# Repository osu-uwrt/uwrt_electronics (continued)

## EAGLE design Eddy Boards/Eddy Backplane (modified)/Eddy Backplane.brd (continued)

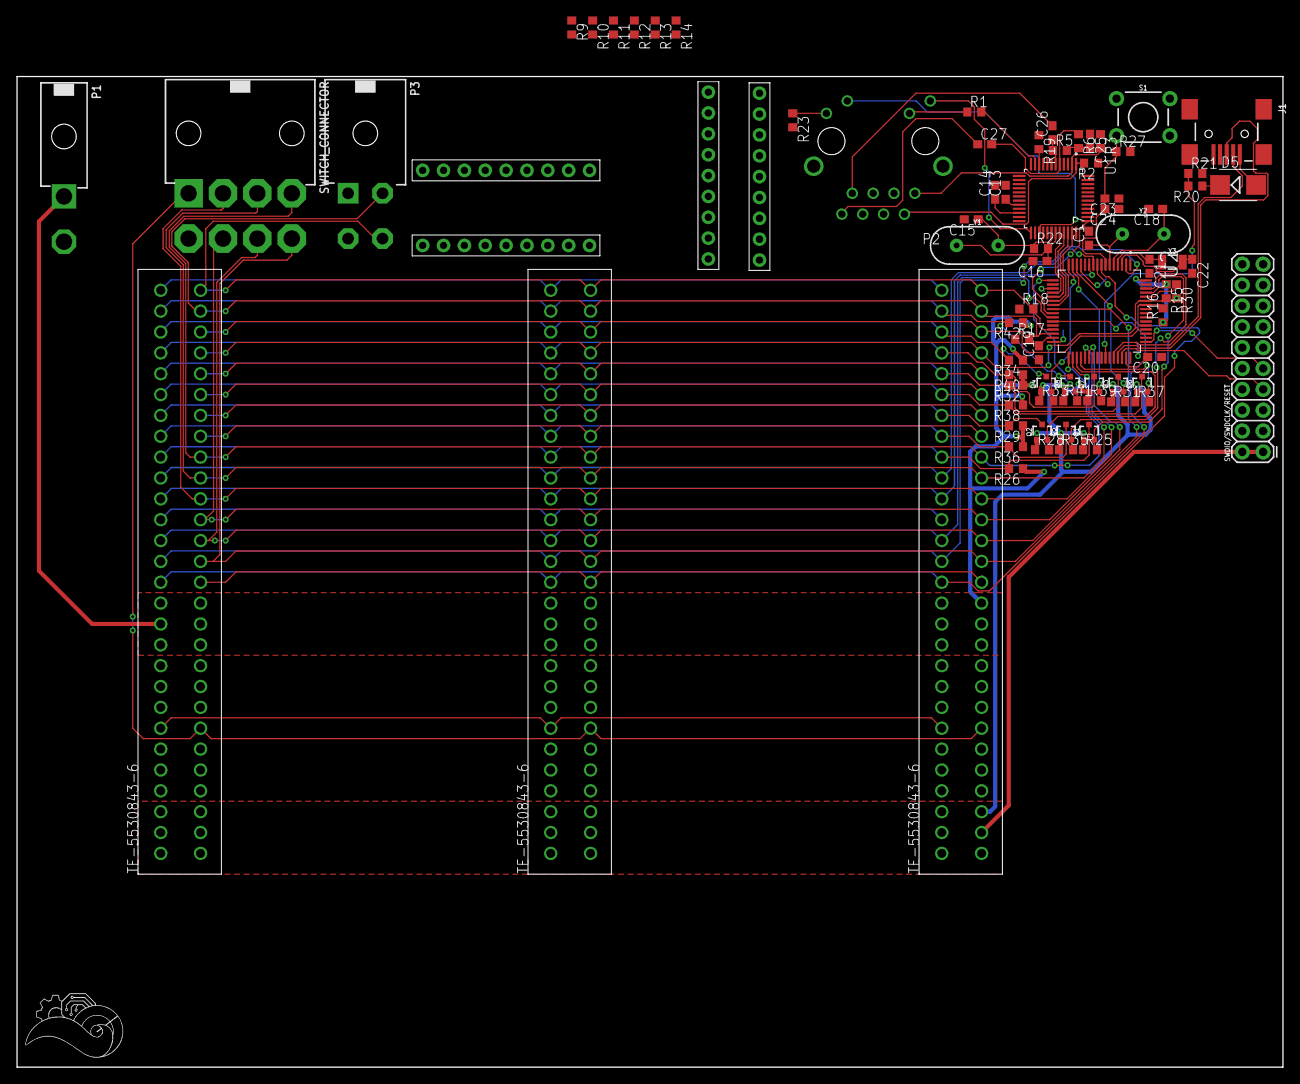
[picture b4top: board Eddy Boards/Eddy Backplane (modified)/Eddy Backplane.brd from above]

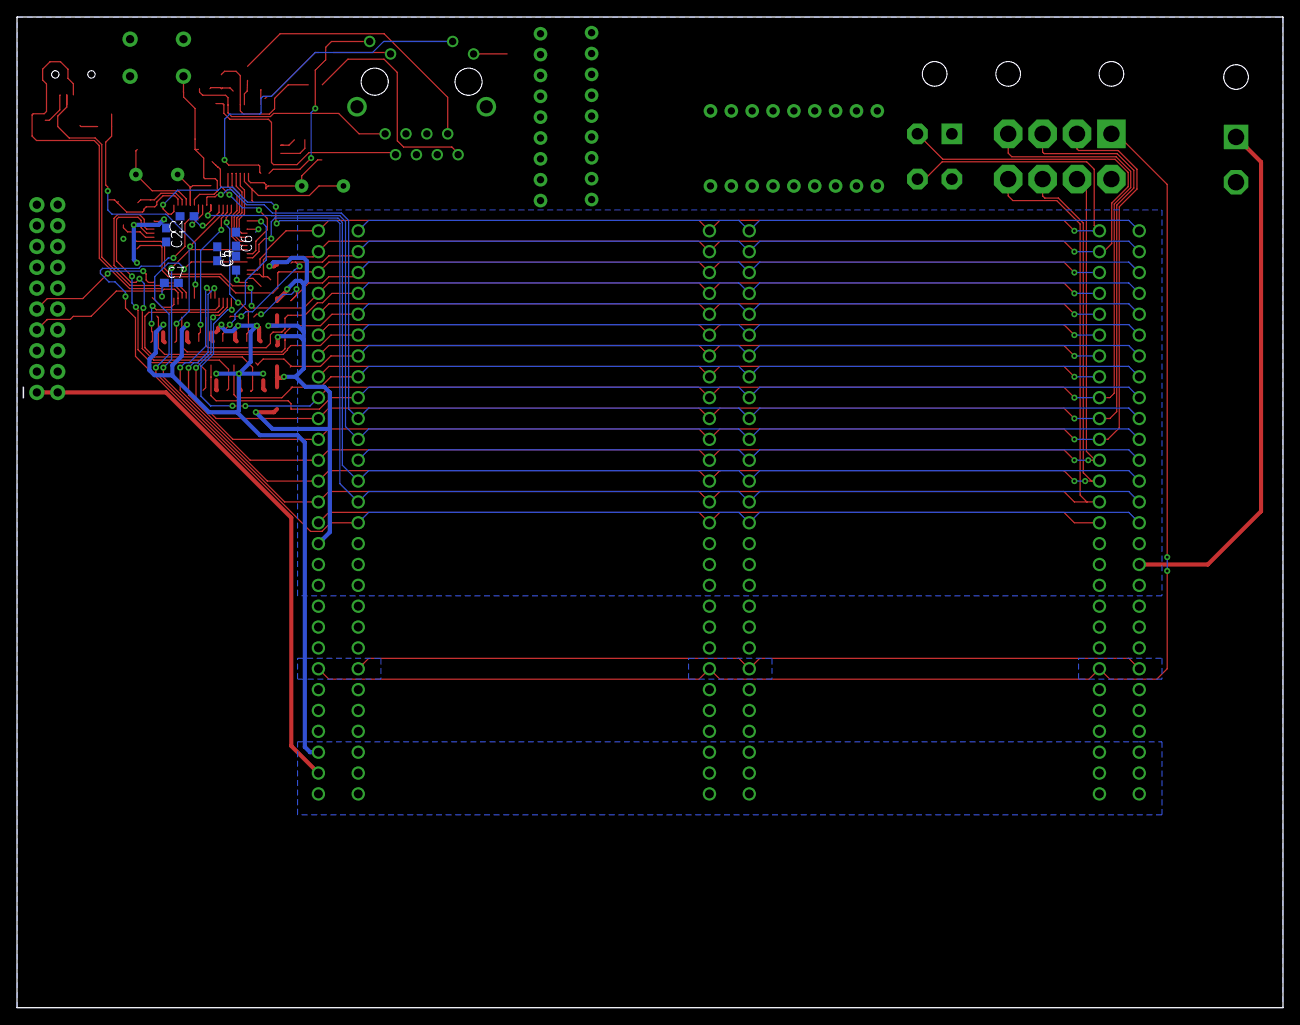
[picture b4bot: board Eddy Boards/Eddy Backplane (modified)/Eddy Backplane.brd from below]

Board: 2 copper layers, 154.2 x 120.7 mm, 87 parts (6 on the bottom side), 79 nets.

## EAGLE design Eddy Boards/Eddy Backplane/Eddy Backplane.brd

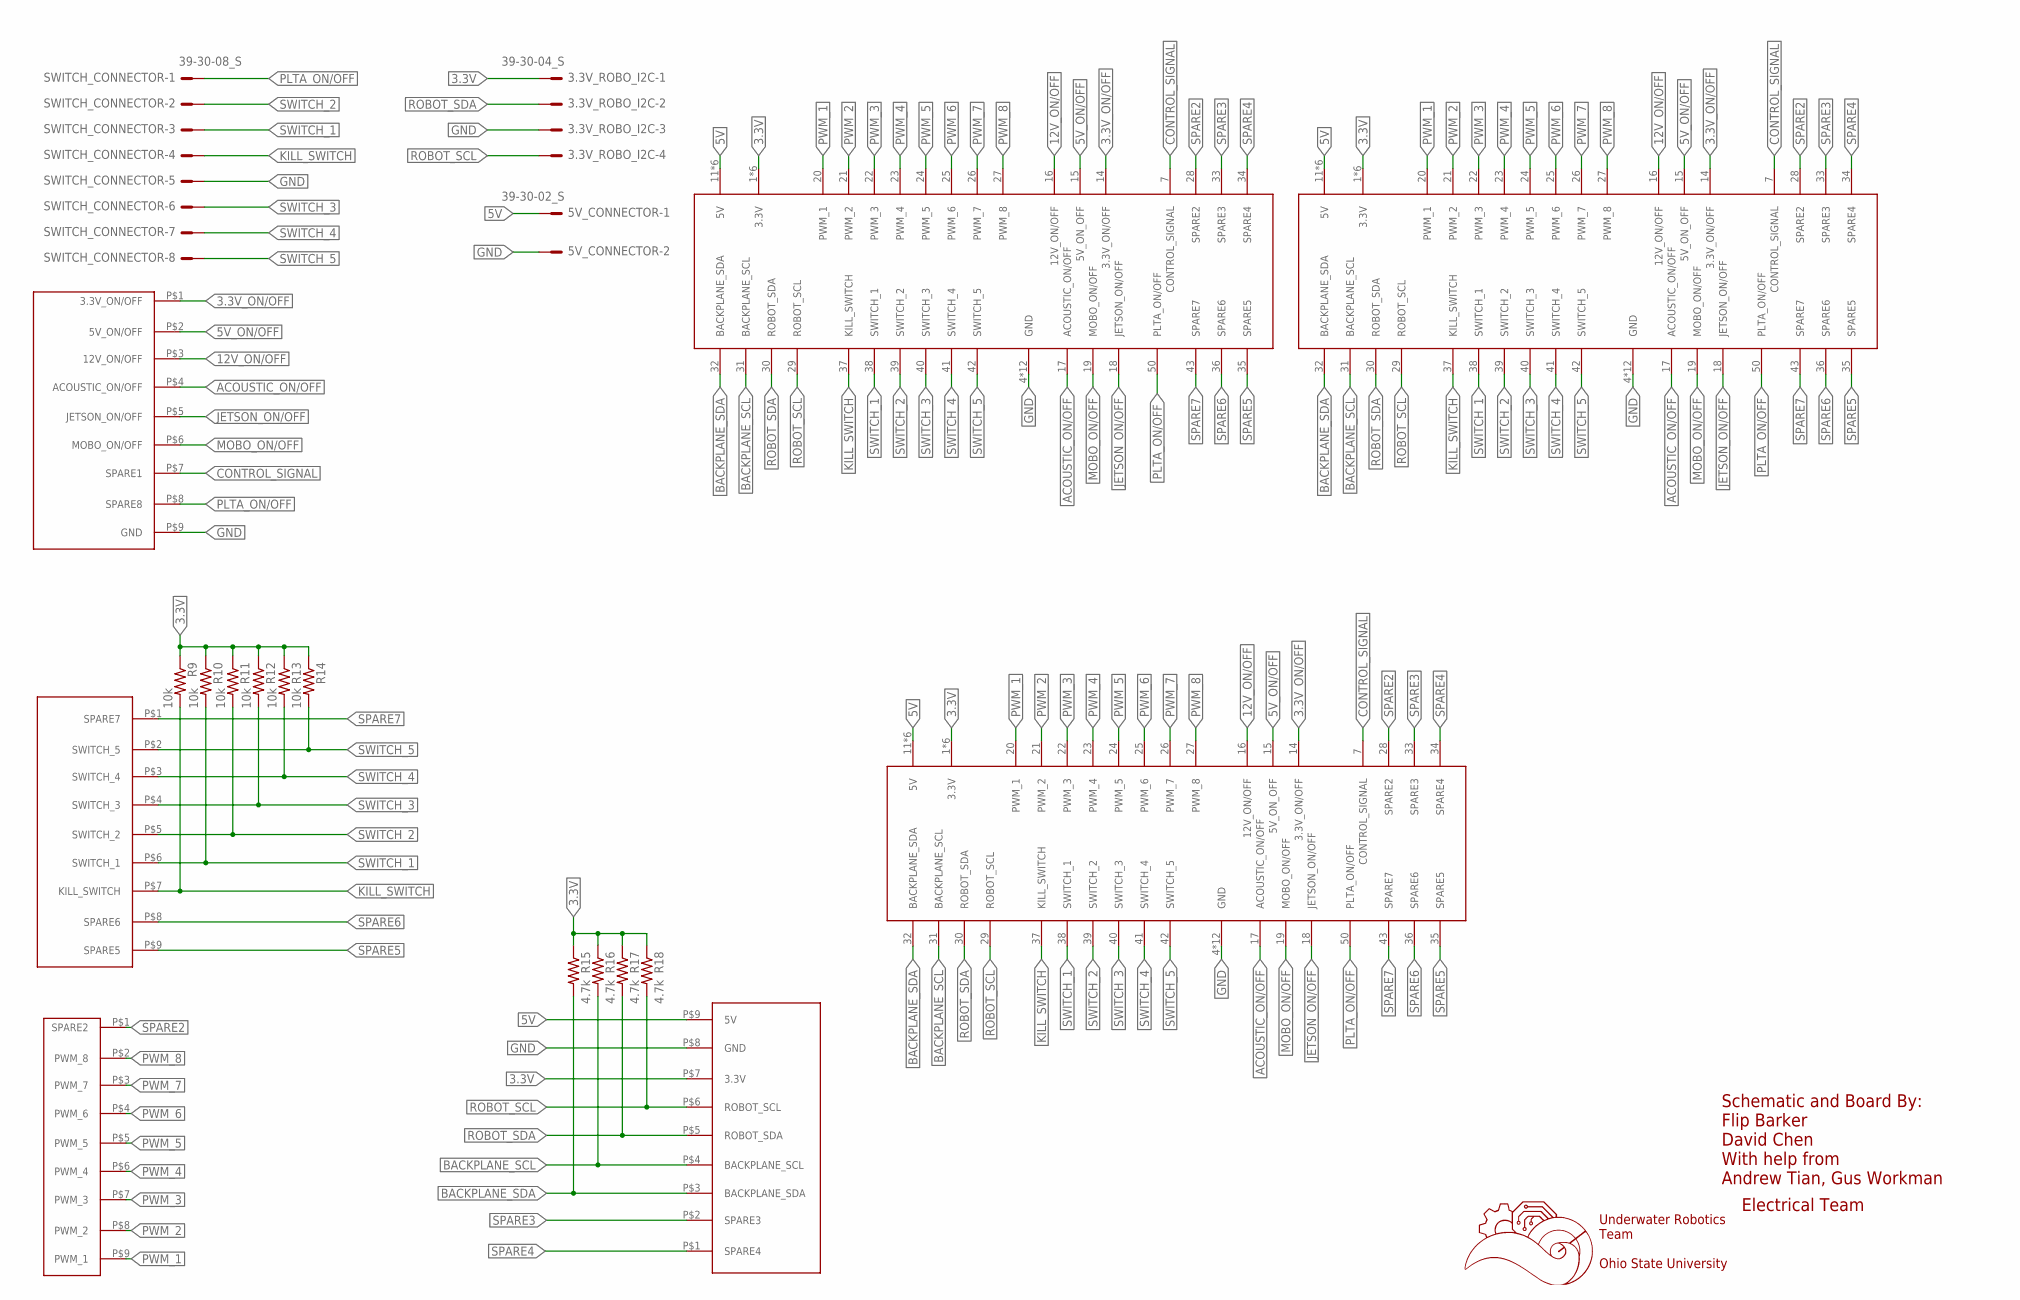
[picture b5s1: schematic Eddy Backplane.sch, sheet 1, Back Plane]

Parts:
3.3V_ROBO_I2C: 39-30-04_S; 39-30-?04?
5V_CONNECTOR: 39-30-02_S; 39-30-?02?
PWR_ON: 929870-01-09_3; 929852-01-09_1ROW
R9, R10, R11, R12, R13, R14: 10k; R0603
R15, R16, R17, R18: 4.7k; R0603
SWITCH_CONN: 929870-01-09_1; 929852-01-09_1ROW
SWITCH_CONNECTOR: 39-30-08_S; 39-30-?08?
U$1, U$2, U$3: 5530843-FEMALE; 5530843-6-BACKPLANEMATE
U$6: 929870-01-09_2; 929852-01-09_1ROW
U$8: 929870-01-09_4; 929852-01-09_1ROW

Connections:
3.3V: 3.3V_ROBO_I2C.1, R9.1, R10.1, R11.1, R12.1, R13.1, R14.1, R15.1, R16.1, R17.1, R18.1, U$1.1 (3.3V), U$1.2 (3.3V), U$1.3 (3.3V), U$1.54 (3.3V), U$1.55 (3.3V), U$1.56 (3.3V), U$2.1 (3.3V), U$2.2 (3.3V), U$2.3 (3.3V), U$2.54 (3.3V), U$2.55 (3.3V), U$2.56 (3.3V), U$3.1 (3.3V), U$3.2 (3.3V), U$3.3 (3.3V), U$3.54 (3.3V), U$3.55 (3.3V), U$3.56 (3.3V), U$8.P$7 (3.3V); also elsewhere on the board
3.3V_ON/OFF: PWR_ON.P$1 (3.3V_ON/OFF), U$1.14 (3.3V_ON/OFF), U$2.14 (3.3V_ON/OFF), U$3.14 (3.3V_ON/OFF); also elsewhere on the board
5V: 5V_CONNECTOR.1, U$1.11 (5V), U$1.12 (5V), U$1.13 (5V), U$1.44 (5V), U$1.45 (5V), U$1.46 (5V), U$2.11 (5V), U$2.12 (5V), U$2.13 (5V), U$2.44 (5V), U$2.45 (5V), U$2.46 (5V), U$3.11 (5V), U$3.12 (5V), U$3.13 (5V), U$3.44 (5V), U$3.45 (5V), U$3.46 (5V), U$8.P$9 (5V); also elsewhere on the board
5V_ON/OFF: PWR_ON.P$2 (5V_ON/OFF), U$1.15 (5V_ON_OFF), U$2.15 (5V_ON_OFF), U$3.15 (5V_ON_OFF); also elsewhere on the board
12V_ON/OFF: PWR_ON.P$3 (12V_ON/OFF), U$1.16 (12V_ON/OFF), U$2.16 (12V_ON/OFF), U$3.16 (12V_ON/OFF); also elsewhere on the board
ACOUSTIC_ON/OFF: PWR_ON.P$4 (ACOUSTIC_ON/OFF), U$1.17 (ACOUSTIC_ON/OFF), U$2.17 (ACOUSTIC_ON/OFF), U$3.17 (ACOUSTIC_ON/OFF)
BACKPLANE_SCL: R16.2, U$1.31 (BACKPLANE_SCL), U$2.31 (BACKPLANE_SCL), U$3.31 (BACKPLANE_SCL), U$8.P$4 (BACKPLANE_SCL); also elsewhere on the board
BACKPLANE_SDA: R15.2, U$1.32 (BACKPLANE_SDA), U$2.32 (BACKPLANE_SDA), U$3.32 (BACKPLANE_SDA), U$8.P$3 (BACKPLANE_SDA); also elsewhere on the board
CONTROL_SIGNAL: PWR_ON.P$7 (SPARE1), U$1.7 (CONTROL_SIGNAL), U$2.7 (CONTROL_SIGNAL), U$3.7 (CONTROL_SIGNAL); also elsewhere on the board
GND: 3.3V_ROBO_I2C.3, 5V_CONNECTOR.2, PWR_ON.P$9 (GND), SWITCH_CONNECTOR.5, U$1.4 (GND), U$1.5 (GND), U$1.6 (GND), U$1.8 (GND), U$1.9 (GND), U$1.10 (GND), U$1.47 (GND), U$1.48 (GND), U$1.49 (GND), U$1.51 (GND), U$1.52 (GND), U$1.53 (GND), U$2.4 (GND), U$2.5 (GND), U$2.6 (GND), U$2.8 (GND), U$2.9 (GND), U$2.10 (GND), U$2.47 (GND), U$2.48 (GND), U$2.49 (GND), U$2.51 (GND), U$2.52 (GND), U$2.53 (GND), U$3.4 (GND), U$3.5 (GND), U$3.6 (GND), U$3.8 (GND), U$3.9 (GND), U$3.10 (GND), U$3.47 (GND), U$3.48 (GND), U$3.49 (GND), U$3.51 (GND), U$3.52 (GND), U$3.53 (GND), U$8.P$8 (GND); also elsewhere on the board
JETSON_ON/OFF: PWR_ON.P$5 (JETSON_ON/OFF), U$1.18 (JETSON_ON/OFF), U$2.18 (JETSON_ON/OFF), U$3.18 (JETSON_ON/OFF); also elsewhere on the board
KILL_SWITCH: R9.2, SWITCH_CONN.P$7 (KILL_SWITCH), SWITCH_CONNECTOR.4, U$1.37 (KILL_SWITCH), U$2.37 (KILL_SWITCH), U$3.37 (KILL_SWITCH); also elsewhere on the board
MOBO_ON/OFF: PWR_ON.P$6 (MOBO_ON/OFF), U$1.19 (MOBO_ON/OFF), U$2.19 (MOBO_ON/OFF), U$3.19 (MOBO_ON/OFF); also elsewhere on the board
PLTA_ON/OFF: PWR_ON.P$8 (SPARE8), SWITCH_CONNECTOR.1, U$1.50 (PLTA_ON/OFF), U$2.50 (PLTA_ON/OFF), U$3.50 (PLTA_ON/OFF)
PWM_1: U$1.20 (PWM_1), U$2.20 (PWM_1), U$3.20 (PWM_1), U$6.P$9 (PWM_1); also elsewhere on the board
PWM_2: U$1.21 (PWM_2), U$2.21 (PWM_2), U$3.21 (PWM_2), U$6.P$8 (PWM_2); also elsewhere on the board
PWM_3: U$1.22 (PWM_3), U$2.22 (PWM_3), U$3.22 (PWM_3), U$6.P$7 (PWM_3); also elsewhere on the board
PWM_4: U$1.23 (PWM_4), U$2.23 (PWM_4), U$3.23 (PWM_4), U$6.P$6 (PWM_4); also elsewhere on the board
PWM_5: U$1.24 (PWM_5), U$2.24 (PWM_5), U$3.24 (PWM_5), U$6.P$5 (PWM_5); also elsewhere on the board
PWM_6: U$1.25 (PWM_6), U$2.25 (PWM_6), U$3.25 (PWM_6), U$6.P$4 (PWM_6); also elsewhere on the board
PWM_7: U$1.26 (PWM_7), U$2.26 (PWM_7), U$3.26 (PWM_7), U$6.P$3 (PWM_7); also elsewhere on the board
PWM_8: U$1.27 (PWM_8), U$2.27 (PWM_8), U$3.27 (PWM_8), U$6.P$2 (PWM_8); also elsewhere on the board
ROBOT_SCL: 3.3V_ROBO_I2C.4, R18.2, U$1.29 (ROBOT_SCL), U$2.29 (ROBOT_SCL), U$3.29 (ROBOT_SCL), U$8.P$6 (ROBOT_SCL); also elsewhere on the board
ROBOT_SDA: 3.3V_ROBO_I2C.2, R17.2, U$1.30 (ROBOT_SDA), U$2.30 (ROBOT_SDA), U$3.30 (ROBOT_SDA), U$8.P$5 (ROBOT_SDA); also elsewhere on the board
SPARE2: U$1.28 (SPARE2), U$2.28 (SPARE2), U$3.28 (SPARE2), U$6.P$1 (SPARE2)
SPARE3: U$1.33 (SPARE3), U$2.33 (SPARE3), U$3.33 (SPARE3), U$8.P$2 (SPARE3)
SPARE4: U$1.34 (SPARE4), U$2.34 (SPARE4), U$3.34 (SPARE4), U$8.P$1 (SPARE4)
SPARE5: SWITCH_CONN.P$9 (SPARE5), U$1.35 (SPARE5), U$2.35 (SPARE5), U$3.35 (SPARE5)
SPARE6: SWITCH_CONN.P$8 (SPARE6), U$1.36 (SPARE6), U$2.36 (SPARE6), U$3.36 (SPARE6)
SPARE7: SWITCH_CONN.P$1 (SPARE7), U$1.43 (SPARE7), U$2.43 (SPARE7), U$3.43 (SPARE7)
SWITCH_1: R10.2, SWITCH_CONN.P$6 (SWITCH_1), SWITCH_CONNECTOR.3, U$1.38 (SWITCH_1), U$2.38 (SWITCH_1), U$3.38 (SWITCH_1); also elsewhere on the board
SWITCH_2: R11.2, SWITCH_CONN.P$5 (SWITCH_2), SWITCH_CONNECTOR.2, U$1.39 (SWITCH_2), U$2.39 (SWITCH_2), U$3.39 (SWITCH_2); also elsewhere on the board
SWITCH_3: R12.2, SWITCH_CONN.P$4 (SWITCH_3), SWITCH_CONNECTOR.6, U$1.40 (SWITCH_3), U$2.40 (SWITCH_3), U$3.40 (SWITCH_3); also elsewhere on the board
SWITCH_4: R13.2, SWITCH_CONN.P$3 (SWITCH_4), SWITCH_CONNECTOR.7, U$1.41 (SWITCH_4), U$2.41 (SWITCH_4), U$3.41 (SWITCH_4); also elsewhere on the board
SWITCH_5: R14.2, SWITCH_CONN.P$2 (SWITCH_5), SWITCH_CONNECTOR.8, U$1.42 (SWITCH_5), U$2.42 (SWITCH_5), U$3.42 (SWITCH_5); also elsewhere on the board

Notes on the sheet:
Underwater Robotics Team Ohio State University
Electrical Team
Schematic and Board By: Flip Barker David Chen With help from Andrew Tian, Gus Workman

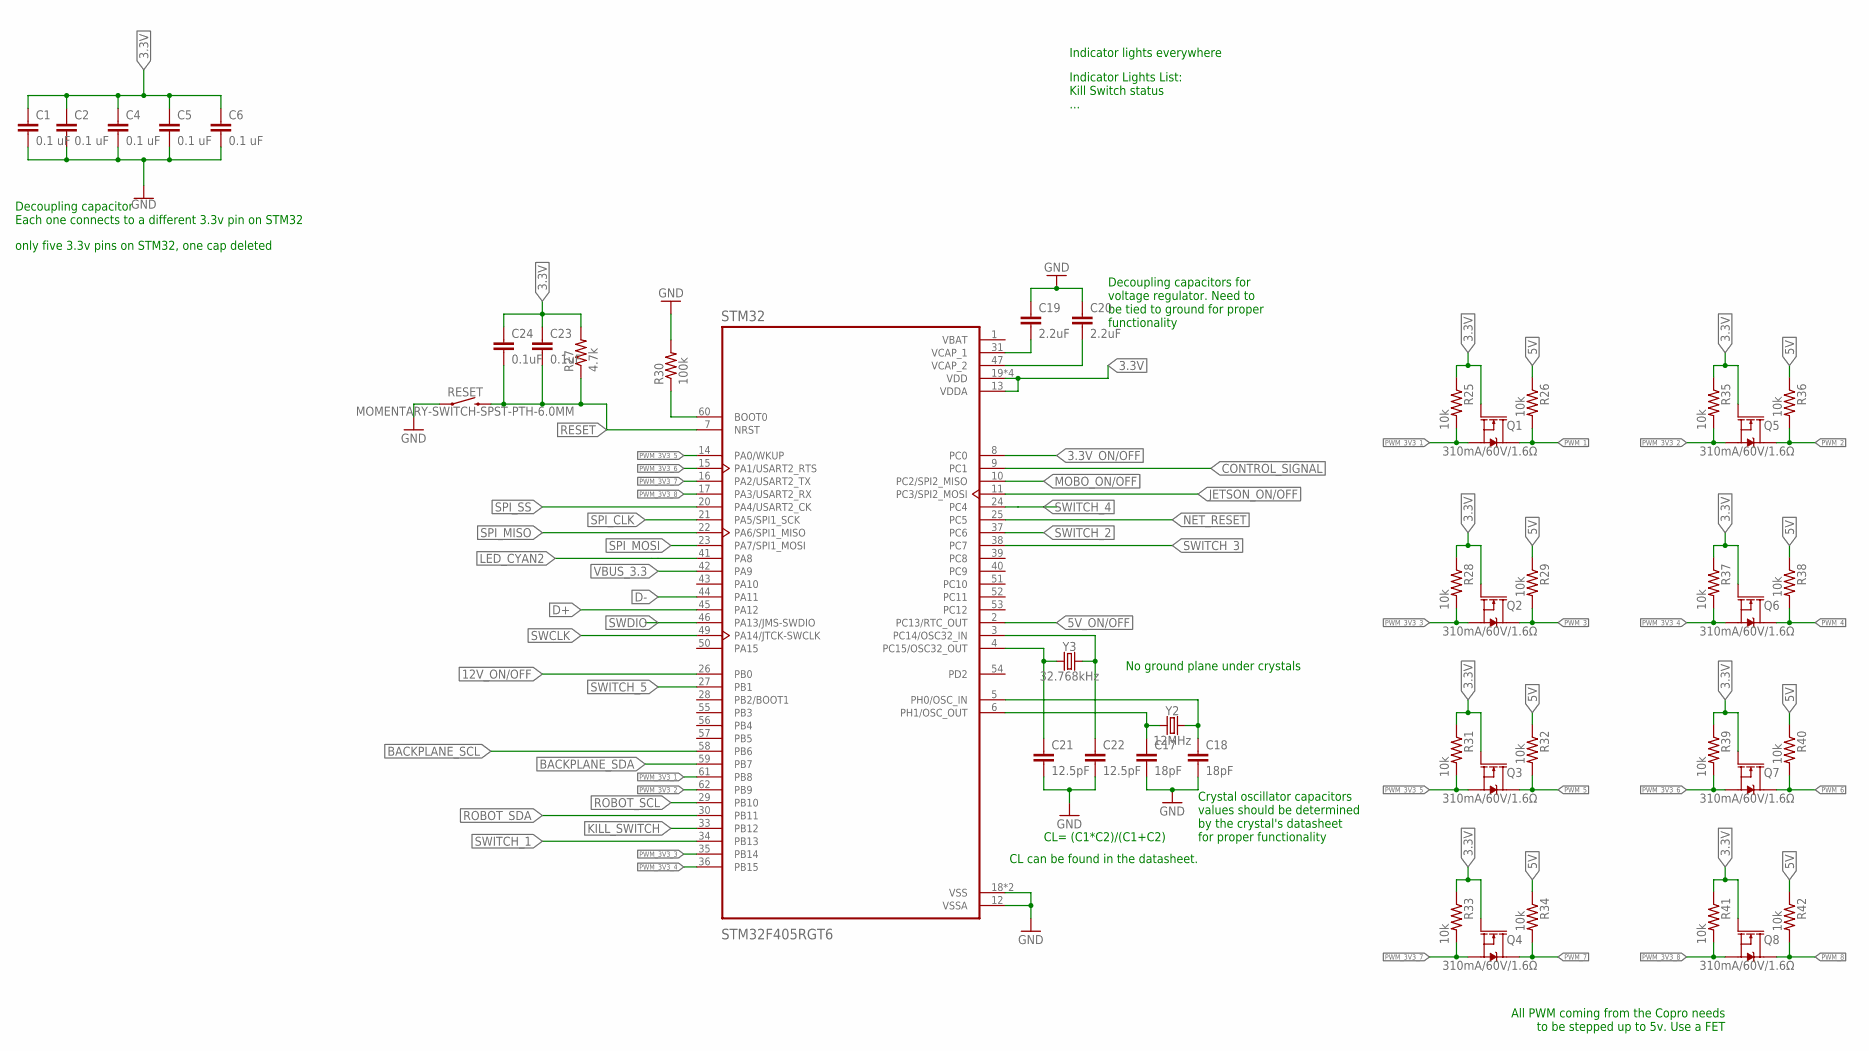
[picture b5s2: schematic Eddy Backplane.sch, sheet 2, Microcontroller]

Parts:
C1, C2, C4, C5, C6: 0.1 uF; C0603
C17, C18: 18pF; C0603
C19, C20: 2.2uF; C0603
C21, C22: 12.5pF; C0603
C23, C24: 0.1uF; C0603
Q1, Q2, Q3, Q4, Q5, Q6, Q7, Q8: 310mA/60V/1.6Ω; SOT323
R25, R26, R28, R29, R31, R32, R33, R34, R35, R36, R37, R38, R39, R40, R41, R42: 10k; R0603
R27: 4.7k; R0603
R30: 100k; R0603
RESET: MOMENTARY-SWITCH-SPST-PTH-6.0MM; TACTILE_SWITCH_PTH_6.0MM
STM32: STM32F405RGT6; QFP50P1200X1200X160-64N
Y2: 12MHz; HC49US
Y3: 32.768kHz; CRYSTAL-SMD-3.2X1.5MM

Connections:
3.3V: C1.1, C2.1, C4.1, C5.1, C6.1, C23.1, C24.1, Q1.1 (G), Q2.1 (G), Q3.1 (G), Q4.1 (G), Q5.1 (G), Q6.1 (G), Q7.1 (G), Q8.1 (G), R25.1, R27.2, R28.1, R31.1, R33.1, R35.1, R37.1, R39.1, R41.1, STM32.13 (VDDA), STM32.19 (VDD), STM32.32 (VDD), STM32.48 (VDD), STM32.64 (VDD); also elsewhere on the board
3.3V_ON/OFF: STM32.8 (PC0); also elsewhere on the board
5V: R26.1, R29.1, R32.1, R34.1, R36.1, R38.1, R40.1, R42.1; also elsewhere on the board
5V_ON/OFF: STM32.2 (PC13/RTC_OUT); also elsewhere on the board
12V_ON/OFF: STM32.26 (PB0); also elsewhere on the board
BACKPLANE_SCL: STM32.58 (PB6); also elsewhere on the board
BACKPLANE_SDA: STM32.59 (PB7); also elsewhere on the board
CONTROL_SIGNAL: STM32.9 (PC1); also elsewhere on the board
D+: STM32.45 (PA12); also elsewhere on the board
D-: STM32.44 (PA11); also elsewhere on the board
GND: C1.2, C2.2, C4.2, C5.2, C6.2, C17.2, C18.2, C19.1, C20.1, C21.2, C22.2, R30.2, RESET.1, STM32.12 (VSSA), STM32.18 (VSS), STM32.63 (VSS); also elsewhere on the board
JETSON_ON/OFF: STM32.11 (PC3/SPI2_MOSI); also elsewhere on the board
KILL_SWITCH: STM32.33 (PB12); also elsewhere on the board
LED_CYAN2: STM32.41 (PA8)
MOBO_ON/OFF: STM32.10 (PC2/SPI2_MISO); also elsewhere on the board
unnamed: C17.1, STM32.6 (PH1/OSC_OUT), Y2.1
unnamed: C18.1, STM32.5 (PH0/OSC_IN), Y2.2
unnamed: C20.2, STM32.47 (VCAP_2)
unnamed: C19.2, STM32.31 (VCAP_1)
unnamed: C21.1, STM32.4 (PC15/OSC32_OUT), Y3.P$1 (1)
unnamed: C22.1, STM32.3 (PC14/OSC32_IN), Y3.P$2 (2)
unnamed: R30.1, STM32.60 (BOOT0)
NET_RESET: STM32.25 (PC5); also elsewhere on the board
PWM_1: Q1.3 (D), R26.2; also elsewhere on the board
PWM_2: Q5.3 (D), R36.2; also elsewhere on the board
PWM_3: Q2.3 (D), R29.2; also elsewhere on the board
PWM_3V3_1: Q1.2 (S), R25.2, STM32.61 (PB8)
PWM_3V3_2: Q5.2 (S), R35.2, STM32.62 (PB9)
PWM_3V3_3: Q2.2 (S), R28.2, STM32.35 (PB14)
PWM_3V3_4: Q6.2 (S), R37.2, STM32.36 (PB15)
PWM_3V3_5: Q3.2 (S), R31.2, STM32.14 (PA0/WKUP)
PWM_3V3_6: Q7.2 (S), R39.2, STM32.15 (PA1/USART2_RTS)
PWM_3V3_7: Q4.2 (S), R33.2, STM32.16 (PA2/USART2_TX)
PWM_3V3_8: Q8.2 (S), R41.2, STM32.17 (PA3/USART2_RX)
PWM_4: Q6.3 (D), R38.2; also elsewhere on the board
PWM_5: Q3.3 (D), R32.2; also elsewhere on the board
PWM_6: Q7.3 (D), R40.2; also elsewhere on the board
PWM_7: Q4.3 (D), R34.2; also elsewhere on the board
PWM_8: Q8.3 (D), R42.2; also elsewhere on the board
RESET: C23.2, C24.2, R27.1, RESET.3 (2), STM32.7 (NRST); also elsewhere on the board
ROBOT_SCL: STM32.29 (PB10); also elsewhere on the board
ROBOT_SDA: STM32.30 (PB11); also elsewhere on the board
SPI_CLK: STM32.21 (PA5/SPI1_SCK); also elsewhere on the board
SPI_MISO: STM32.22 (PA6/SPI1_MISO); also elsewhere on the board
SPI_MOSI: STM32.23 (PA7/SPI1_MOSI); also elsewhere on the board
SPI_SS: STM32.20 (PA4/USART2_CK); also elsewhere on the board
SWCLK: STM32.49 (PA14/JTCK-SWCLK); also elsewhere on the board
SWDIO: STM32.46 (PA13/JMS-SWDIO); also elsewhere on the board
SWITCH_1: STM32.34 (PB13); also elsewhere on the board
SWITCH_2: STM32.37 (PC6); also elsewhere on the board
SWITCH_3: STM32.38 (PC7); also elsewhere on the board
SWITCH_4: STM32.24 (PC4); also elsewhere on the board
SWITCH_5: STM32.27 (PB1); also elsewhere on the board
VBAT: STM32.1 (VBAT)
VBUS_3.3: STM32.42 (PA9); also elsewhere on the board

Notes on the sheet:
Decoupling capacitor Each one connects to a different 3.3v pin on STM32
Indicator lights everywhere
Decoupling capacitors for voltage regulator. Need to be tied to ground for proper functionality
Crystal oscillator capacitors values should be determined by the crystal's datasheet for proper functionality
All PWM coming from the Copro needs to be stepped up to 5v. Use a FET
CL= (C1*C2)/(C1+C2)
CL can be found in the datasheet.
No ground plane under crystals
Indicator Lights List: Kill Switch status ...
only five 3.3v pins on STM32, one cap deleted

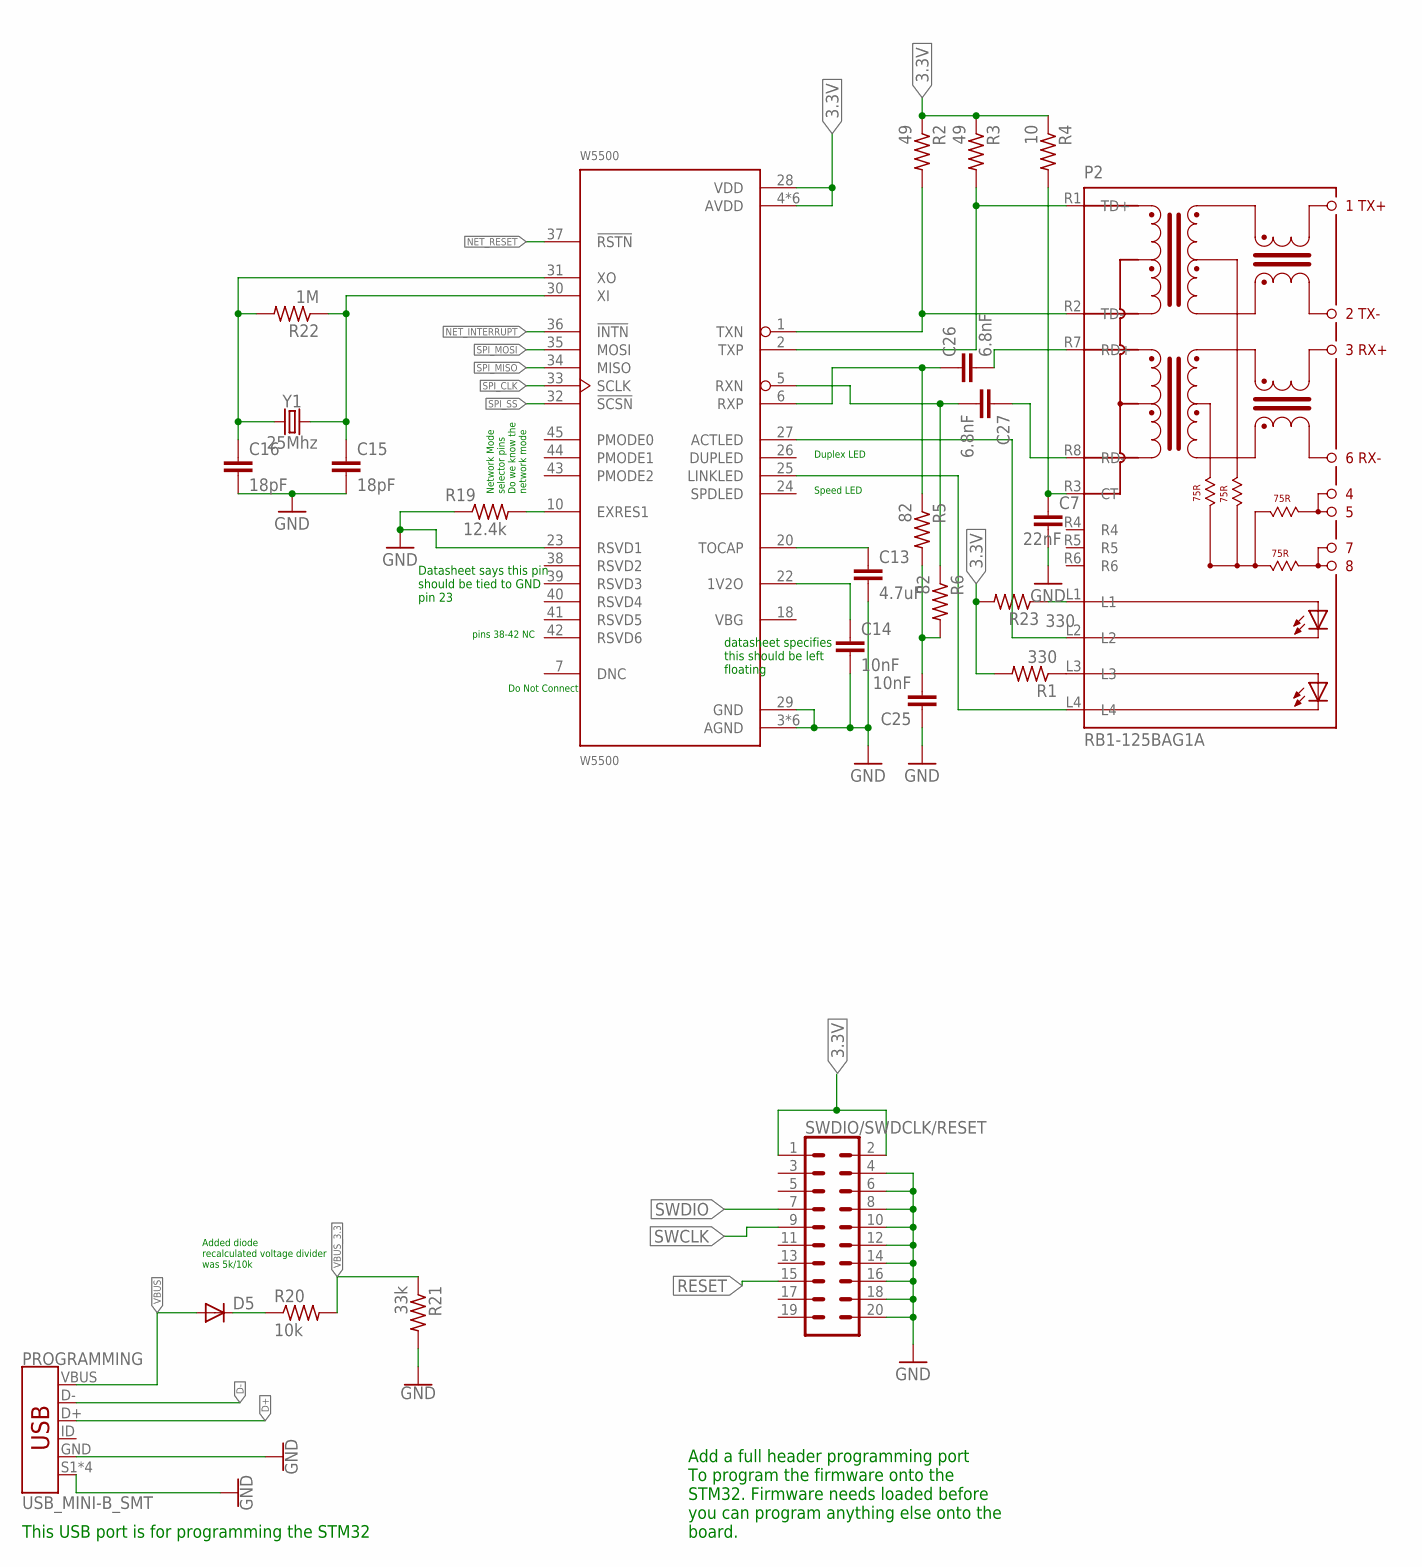
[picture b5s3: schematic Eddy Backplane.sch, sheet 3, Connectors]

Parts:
C7: 22nF; C0603
C13: 4.7uF; C0603
C14, C25: 10nF; C0603
C15, C16: 18pF; C0603
C26, C27: 6.8nF; C0603
D5: DIODE-SMB; SMB
P2: RB1-125BAG1A; WIZNET_RB1-125BAG1A
PROGRAMMING: USB_MINI-B_SMT; USB-MINIB
R1, R23: 330; R0603
R2, R3: 49; R0603
R4: 10; R0603
R5, R6: 82; R0603
R19: 12.4k; R0603
R20: 10k; R0603
R21: 33k; R0603
R22: 1M; R0603
SWDIO/SWDCLK/RESET: CONN_10X2; 2X10
W5500: W5500; QFP50P900X900X160-48N
Y1: 25Mhz; HC49US

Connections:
3.3V: R1.2, R2.1, R3.1, R4.1, R23.2, SWDIO/SWDCLK/RESET.1, SWDIO/SWDCLK/RESET.2, W5500.4 (AVDD), W5500.8 (AVDD), W5500.11 (AVDD), W5500.15 (AVDD), W5500.17 (AVDD), W5500.21 (AVDD), W5500.28 (VDD); also elsewhere on the board
D+: PROGRAMMING.D+; also elsewhere on the board
D-: PROGRAMMING.D-; also elsewhere on the board
GND: C7.2, C13.2, C14.2, C15.2, C16.2, C25.1, PROGRAMMING.GND, PROGRAMMING.S1 (SHIELD), PROGRAMMING.S2 (SHIELD), PROGRAMMING.S3 (SHIELD), PROGRAMMING.S4 (SHIELD), R19.1, R21.2, SWDIO/SWDCLK/RESET.4, SWDIO/SWDCLK/RESET.6, SWDIO/SWDCLK/RESET.8, SWDIO/SWDCLK/RESET.10, SWDIO/SWDCLK/RESET.12, SWDIO/SWDCLK/RESET.14, SWDIO/SWDCLK/RESET.16, SWDIO/SWDCLK/RESET.18, SWDIO/SWDCLK/RESET.20, W5500.3 (AGND), W5500.9 (AGND), W5500.14 (AGND), W5500.16 (AGND), W5500.19 (AGND), W5500.23 (RSVD1), W5500.29 (GND), W5500.48 (AGND); also elsewhere on the board
unnamed: C7.1, P2.R3 (CT), R4.2
unnamed: C14.1, W5500.22 (1V2O)
unnamed: D5.C, R20.1
unnamed: C15.1, R22.1, W5500.30 (XI), Y1.2
unnamed: C16.1, R22.2, W5500.31 (XO), Y1.1
unnamed: P2.L4, W5500.25 (LINKLED)
unnamed: P2.L2, W5500.27 (ACTLED)
unnamed: C13.1, W5500.20 (TOCAP)
unnamed: R19.2, W5500.10 (EXRES1)
unnamed: P2.L1, R23.1
unnamed: P2.L3, R1.1
unnamed: C25.2, R5.2, R6.2
unnamed: P2.R1 (TD+), R3.2, W5500.2 (TXP)
unnamed: P2.R2 (TD-), R2.2, W5500.1 (TXN)
unnamed: C26.2, P2.R7 (RD+)
unnamed: C26.1, R5.1, W5500.6 (RXP)
unnamed: C27.2, R6.1, W5500.5 (RXN)
unnamed: C27.1, P2.R8 (RD-)
NET_INTERRUPT: W5500.36 (!INTN)
NET_RESET: W5500.37 (!RSTN); also elsewhere on the board
RESET: SWDIO/SWDCLK/RESET.15; also elsewhere on the board
SPI_CLK: W5500.33 (SCLK); also elsewhere on the board
SPI_MISO: W5500.34 (MISO); also elsewhere on the board
SPI_MOSI: W5500.35 (MOSI); also elsewhere on the board
SPI_SS: W5500.32 (!SCSN); also elsewhere on the board
SWCLK: SWDIO/SWDCLK/RESET.9; also elsewhere on the board
SWDIO: SWDIO/SWDCLK/RESET.7; also elsewhere on the board
VBUS: D5.A, PROGRAMMING.VBUS
VBUS_3.3: R20.2, R21.1; also elsewhere on the board

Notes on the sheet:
This USB port is for programming the STM32
Add a full header programming port To program the firmware onto the STM32. Firmware needs loaded before you can program anything else onto the board.
datasheet specifies this should be left floating
Datasheet says this pin should be tied to GND pin 23
pins 38-42 NC
Do Not Connect
Duplex LED
Speed LED
Network Mode selector pins Do we know the network mode
Added diode recalculated voltage divider was 5k/10k

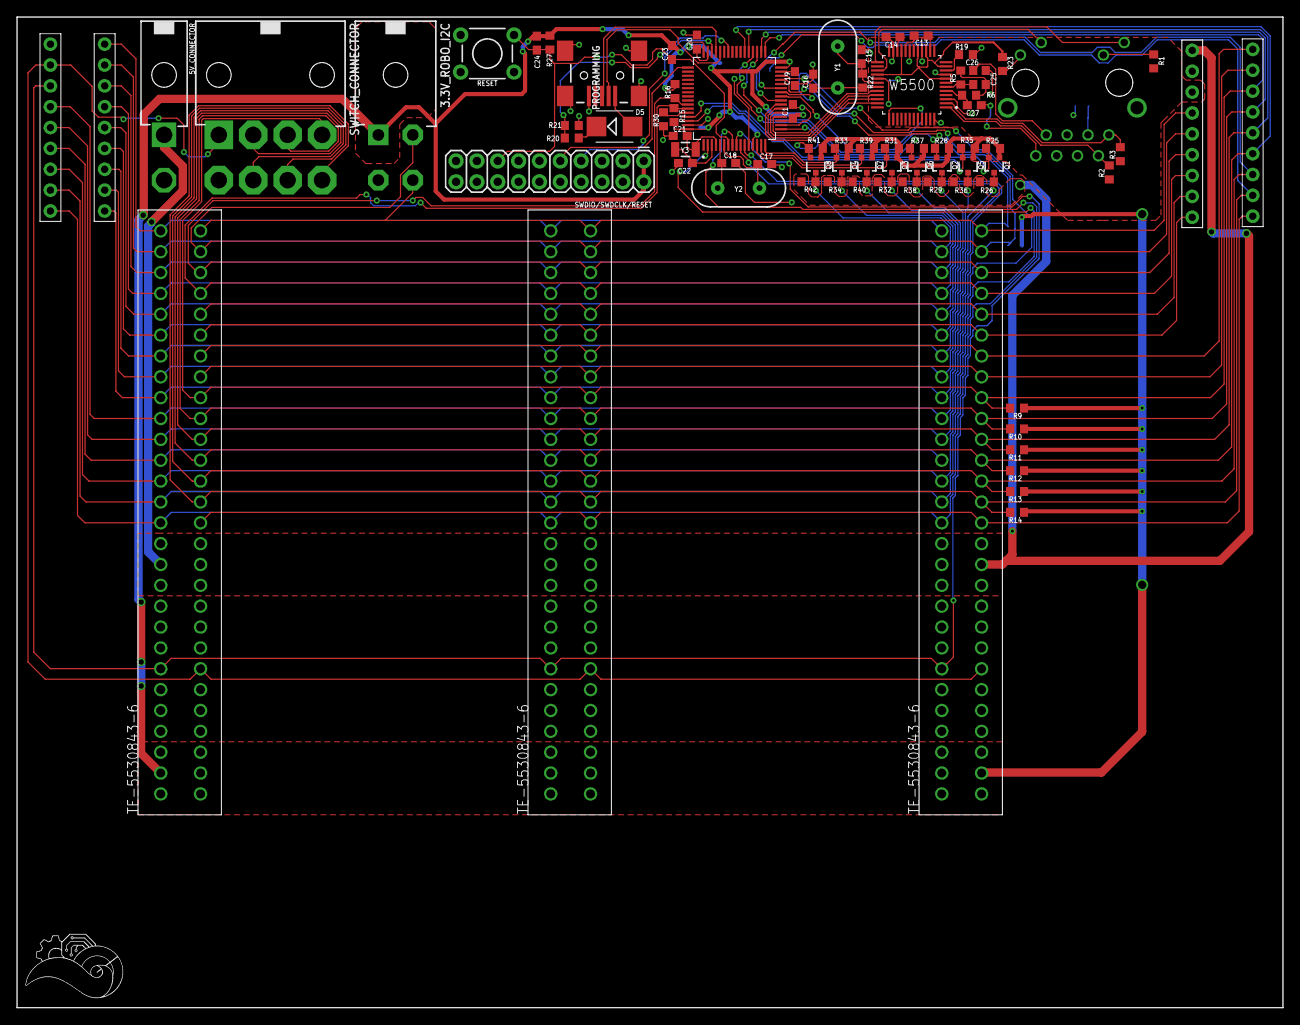
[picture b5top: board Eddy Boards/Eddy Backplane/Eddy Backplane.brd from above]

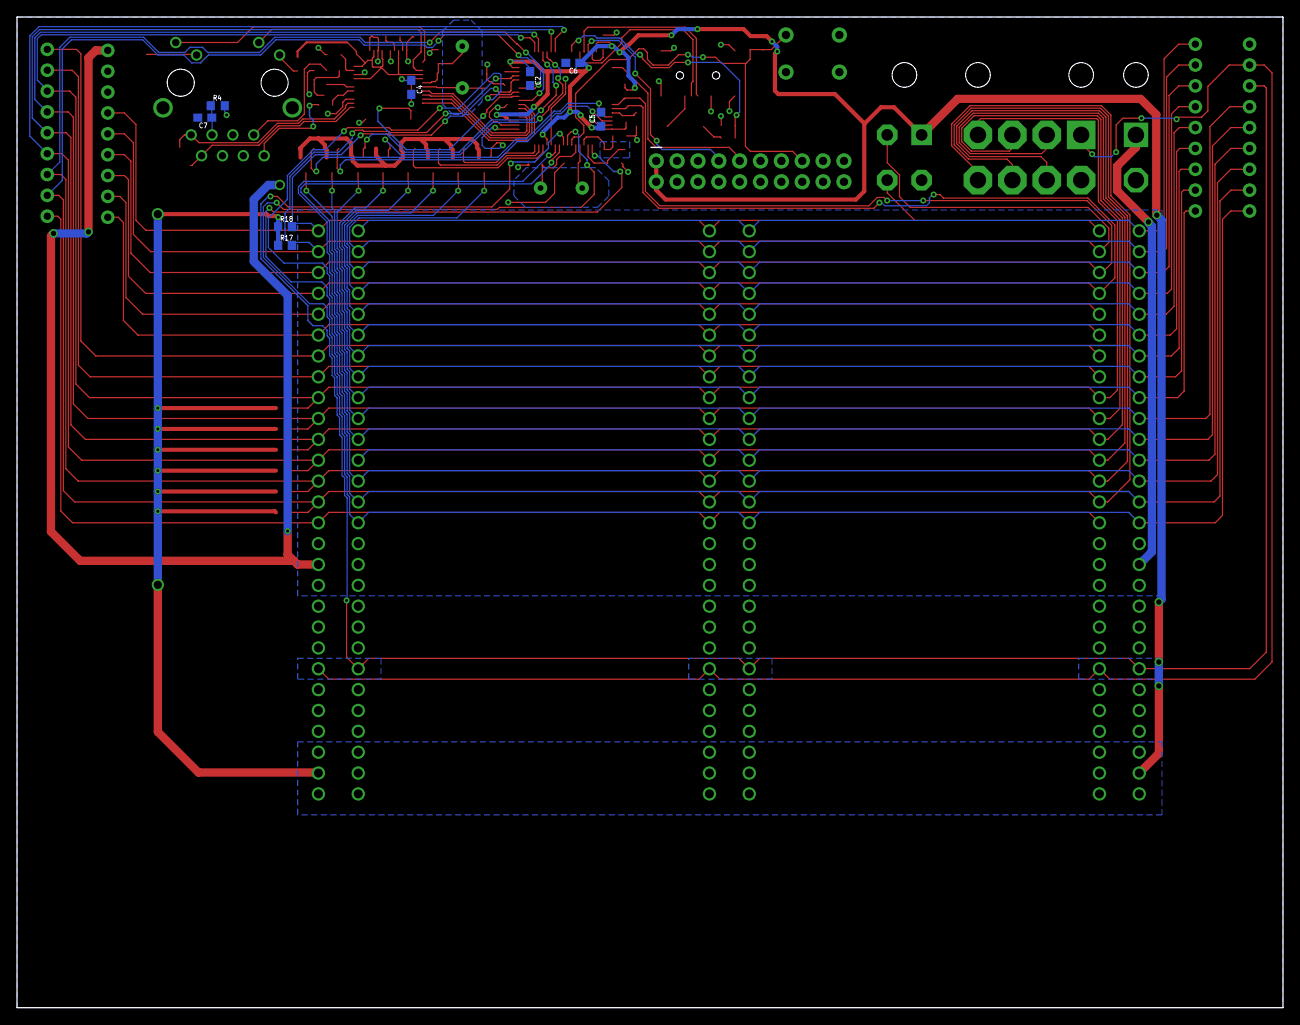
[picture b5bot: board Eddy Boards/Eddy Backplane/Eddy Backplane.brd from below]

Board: 2 copper layers, 154.2 x 120.7 mm, 88 parts (8 on the bottom side), 80 nets.
